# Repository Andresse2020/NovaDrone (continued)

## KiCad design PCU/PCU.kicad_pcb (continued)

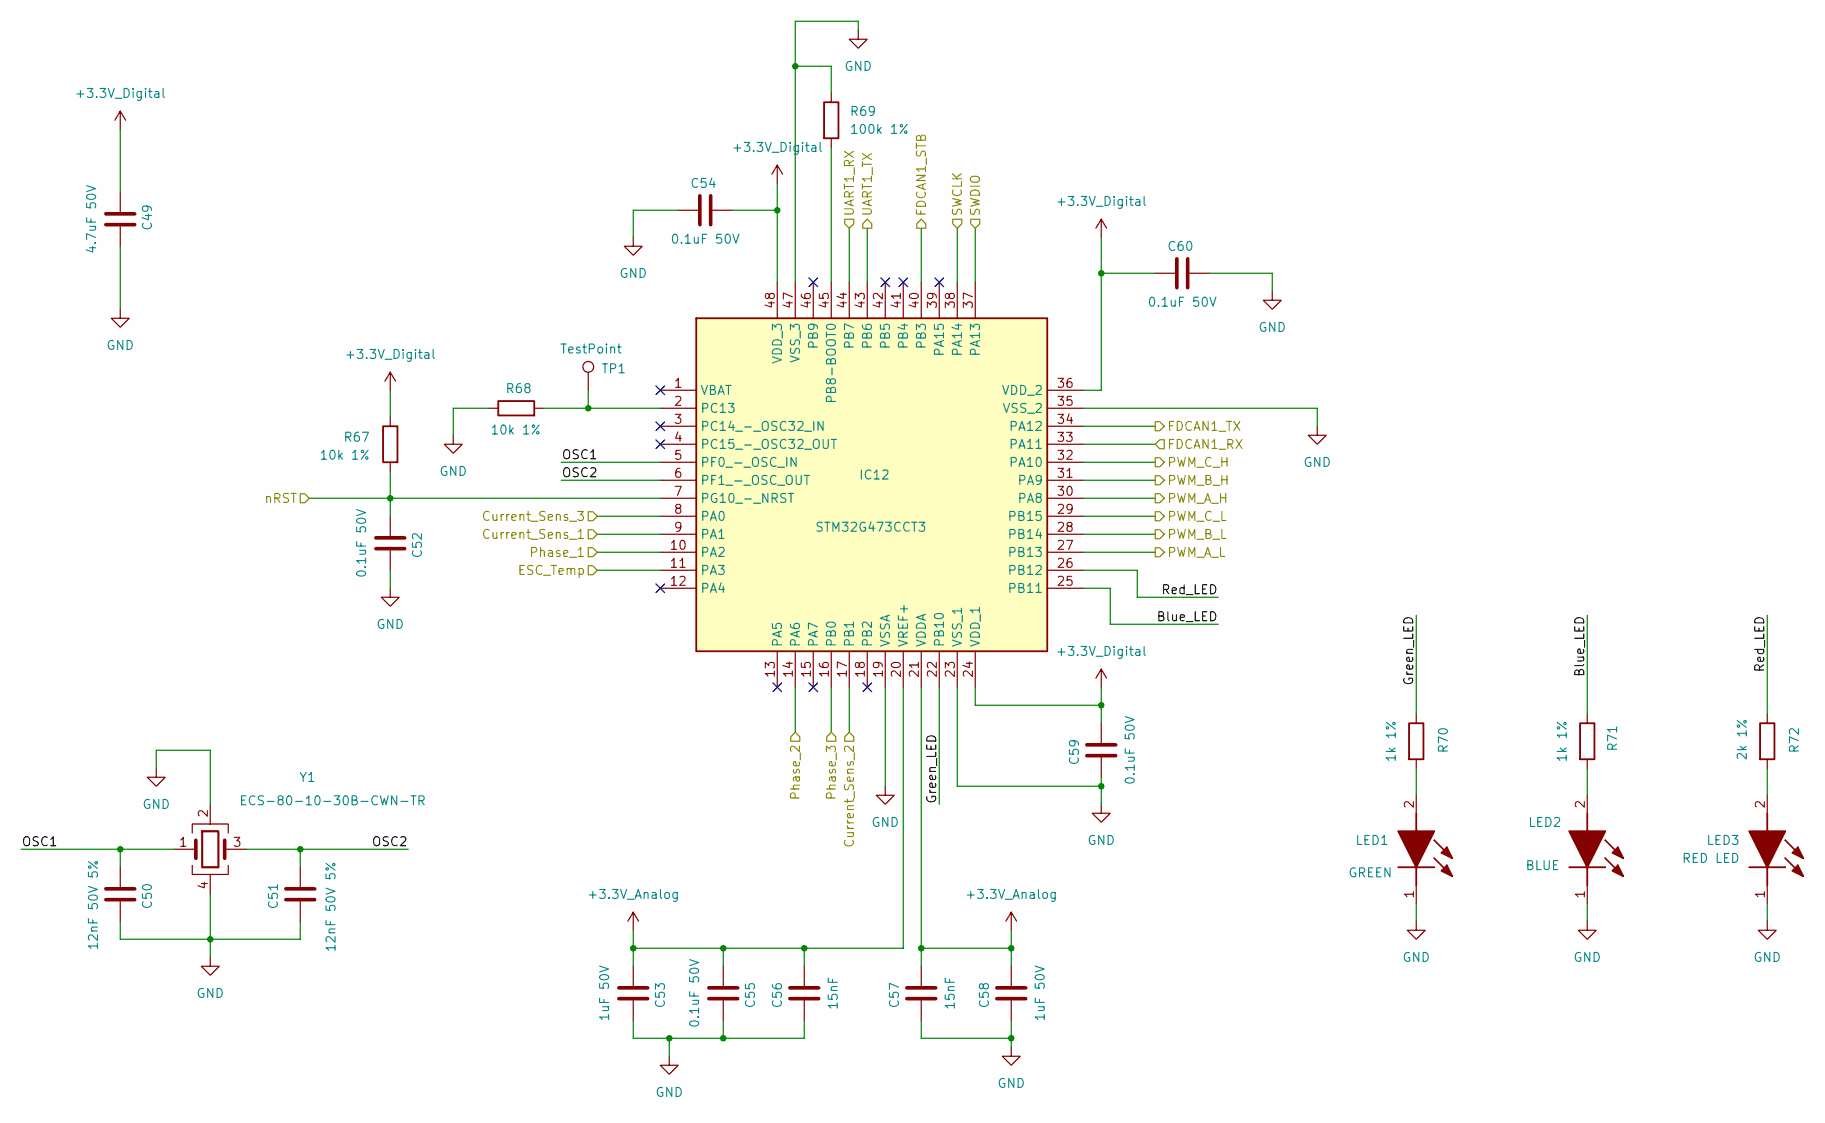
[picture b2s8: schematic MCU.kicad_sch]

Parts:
C49: 4.7uF 50V; C_1206_3216Metric; Manufacturer_Part_Number CL31B475KBHNFNE
C50, C51: 12nF 50V 5%; C_0603_1608Metric; Manufacturer_Part_Number 06035C120J4T2A
C52, C54, C55, C59, C60: 0.1uF 50V; C_0603_1608Metric; Manufacturer_Part_Number CL10B104KB85PNL
C53, C58: 1uF 50V; C_0805_2012Metric; Manufacturer_Part_Number CL21B105KBFNNNE
C56, C57: 15nF; C_0603_1608Metric; Manufacturer_Part_Number CL10B153KB8NNNC
IC12: STM32G473CCT3; QFP50P900X900X160-48N; Mouser Part Number 511-STM32G473CCT3
LED1: GREEN; LEDM168X80N; Mouser Part Number 604-APHD1608LZGCK
LED2: BLUE; LEDM168X80N; Mouser Part Number 604-APHD1608LQBCD
LED3: RED LED; LEDM168X80N; Manufacturer_Part_Number APHD1608LSURCK
R67, R68: 10k 1%; R_0603_1608Metric; Manufacturer_Part_Number AF0603FR-0710KL
R69: 100k 1%; R_0603_1608Metric; Manufacturer_Part_Number AT0603FRE07100KL
R70, R71: 1k 1%; R_0603_1608Metric; Manufacturer_Part_Number RT0603FRE071KL
R72: 2k 1%; R_0603_1608Metric; Manufacturer_Part_Number RE0603FRE072KL
TP1: TestPoint; TestPoint_Pad_D1.0mm
Y1: ECS-80-10-30B-CWN-TR; ECS801830BAGNTR; Mouser Part Number 520-80-10-30B-CWNT

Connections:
+3.3V_Analog: C53.2, C55.2, C56.2, C57.2, C58.2, IC12.20 (VREF+), IC12.21 (VDDA); also elsewhere on the board
+3.3V_Digital: C49.1, C54.2, C59.2, C60.1, IC12.24 (VDD_1), IC12.36 (VDD_2), IC12.48 (VDD_3), R67.1; also elsewhere on the board
/ESC_2/Current_Sens_1: IC12.9 (PA1); also elsewhere on the board
/ESC_2/Current_Sens_2: IC12.17 (PB1); also elsewhere on the board
/ESC_2/Current_Sens_3: IC12.8 (PA0); also elsewhere on the board
/ESC_2/ESC_Temp: IC12.11 (PA3); also elsewhere on the board
/ESC_2/MCU/Blue_LED: IC12.25 (PB11), R71.1
/ESC_2/MCU/FDCAN1_RX: IC12.33 (PA11); also elsewhere on the board
/ESC_2/MCU/FDCAN1_STB: IC12.40 (PB3); also elsewhere on the board
/ESC_2/MCU/FDCAN1_TX: IC12.34 (PA12); also elsewhere on the board
/ESC_2/MCU/Green_LED: IC12.22 (PB10), R70.1
/ESC_2/MCU/OSC1: C50.2, IC12.5 (PF0_-_OSC_IN), Y1.1
/ESC_2/MCU/OSC2: C51.2, IC12.6 (PF1_-_OSC_OUT), Y1.3
/ESC_2/MCU/PWM_A_H: IC12.30 (PA8); also elsewhere on the board
/ESC_2/MCU/PWM_A_L: IC12.27 (PB13); also elsewhere on the board
/ESC_2/MCU/PWM_B_H: IC12.31 (PA9); also elsewhere on the board
/ESC_2/MCU/PWM_B_L: IC12.28 (PB14); also elsewhere on the board
/ESC_2/MCU/PWM_C_H: IC12.32 (PA10); also elsewhere on the board
/ESC_2/MCU/PWM_C_L: IC12.29 (PB15); also elsewhere on the board
/ESC_2/MCU/Red_LED: IC12.26 (PB12), R72.1
/ESC_2/MCU/SWCLK: IC12.38 (PA14); also elsewhere on the board
/ESC_2/MCU/SWDIO: IC12.37 (PA13); also elsewhere on the board
/ESC_2/MCU/UART1_RX: IC12.44 (PB7); also elsewhere on the board
/ESC_2/MCU/UART1_TX: IC12.43 (PB6); also elsewhere on the board
/ESC_2/Phase_1: IC12.10 (PA2); also elsewhere on the board
/ESC_2/Phase_2: IC12.14 (PA6); also elsewhere on the board
/ESC_2/Phase_3: IC12.16 (PB0); also elsewhere on the board
/ESC_2_nRST: C52.2, IC12.7 (PG10_-_NRST), R67.2; also elsewhere on the board
GND: C49.2, C50.1, C51.1, C52.1, C53.1, C54.1, C55.1, C56.1, C57.1, C58.1, C59.1, C60.2, IC12.19 (VSSA), IC12.23 (VSS_1), IC12.35 (VSS_2), IC12.47 (VSS_3), LED1.1 (K), LED2.1 (K), LED3.1 (K), R68.1, R69.1, Y1.2, Y1.4; also elsewhere on the board
unnamed: IC12.45 (PB8-BOOT0), R69.2
unnamed: IC12.2 (PC13), R68.2, TP1.1
unnamed: LED1.2 (A), R70.2
unnamed: LED2.2 (A), R71.2
unnamed: LED3.2 (A), R72.2

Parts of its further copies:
C97, C145, C181: 4.7uF 50V; C_1206_3216Metric; Manufacturer_Part_Number CL31B475KBHNFNE
C98, C99, C146, C147, C182, C183: 12nF 50V 5%; C_0603_1608Metric; Manufacturer_Part_Number 06035C120J4T2A
C100, C102, C103, C107, C108, C148, C150, C151, C155, C156, C184, C186, C187, C191, C192: 0.1uF 50V; C_0603_1608Metric; Manufacturer_Part_Number CL10B104KB85PNL
C101, C106, C149, C154, C185, C190: 1uF 50V; C_0805_2012Metric; Manufacturer_Part_Number CL21B105KBFNNNE
C104, C105, C152, C153, C188, C189: 15nF; C_0603_1608Metric; Manufacturer_Part_Number CL10B153KB8NNNC
IC20, IC28, IC30: STM32G473CCT3; QFP50P900X900X160-48N; Mouser Part Number 511-STM32G473CCT3
LED4, LED7, LED13: GREEN; LEDM168X80N; Mouser Part Number 604-APHD1608LZGCK
LED5, LED8, LED14: BLUE; LEDM168X80N; Mouser Part Number 604-APHD1608LQBCD
LED6, LED9, LED15: RED LED; LEDM168X80N; Manufacturer_Part_Number APHD1608LSURCK
R125, R126, R183, R184, R201, R202: 10k 1%; R_0603_1608Metric; Manufacturer_Part_Number AF0603FR-0710KL
R127, R185, R203: 100k 1%; R_0603_1608Metric; Manufacturer_Part_Number AT0603FRE07100KL
R128, R129, R186, R187, R204, R205: 1k 1%; R_0603_1608Metric; Manufacturer_Part_Number RT0603FRE071KL
R130, R188, R206: 2k 1%; R_0603_1608Metric; Manufacturer_Part_Number RE0603FRE072KL
TP2, TP3, TP7: TestPoint; TestPoint_Pad_D1.0mm
Y2, Y3, Y4: ECS-80-10-30B-CWN-TR; ECS801830BAGNTR; Mouser Part Number 520-80-10-30B-CWNT

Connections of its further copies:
+3.3V_Analog: C101.2, C103.2, C104.2, C105.2, C106.2, C149.2, C151.2, C152.2, C153.2, C154.2, C185.2, C187.2, C188.2, C189.2, C190.2, IC20.20 (VREF+), IC20.21 (VDDA), IC28.20 (VREF+), IC28.21 (VDDA), IC30.20 (VREF+), IC30.21 (VDDA); also elsewhere on the board
+3.3V_Digital: C97.1, C102.2, C107.2, C108.1, C145.1, C150.2, C155.2, C156.1, C181.1, C186.2, C191.2, C192.1, IC20.24 (VDD_1), IC20.36 (VDD_2), IC20.48 (VDD_3), IC28.24 (VDD_1), IC28.36 (VDD_2), IC28.48 (VDD_3), IC30.24 (VDD_1), IC30.36 (VDD_2), IC30.48 (VDD_3), R125.1, R183.1, R201.1; also elsewhere on the board
/ESC_1/Current_Sens_1: IC30.9 (PA1); also elsewhere on the board
/ESC_1/Current_Sens_2: IC30.17 (PB1); also elsewhere on the board
/ESC_1/Current_Sens_3: IC30.8 (PA0); also elsewhere on the board
/ESC_1/ESC_Temp: IC30.11 (PA3); also elsewhere on the board
/ESC_1/MCU/Blue_LED: IC30.25 (PB11), R205.1
/ESC_1/MCU/FDCAN1_RX: IC30.33 (PA11); also elsewhere on the board
/ESC_1/MCU/FDCAN1_STB: IC30.40 (PB3); also elsewhere on the board
/ESC_1/MCU/FDCAN1_TX: IC30.34 (PA12); also elsewhere on the board
/ESC_1/MCU/Green_LED: IC30.22 (PB10), R204.1
/ESC_1/MCU/OSC1: C182.2, IC30.5 (PF0_-_OSC_IN), Y4.1
/ESC_1/MCU/OSC2: C183.2, IC30.6 (PF1_-_OSC_OUT), Y4.3
/ESC_1/MCU/PWM_A_H: IC30.30 (PA8); also elsewhere on the board
/ESC_1/MCU/PWM_A_L: IC30.27 (PB13); also elsewhere on the board
/ESC_1/MCU/PWM_B_H: IC30.31 (PA9); also elsewhere on the board
/ESC_1/MCU/PWM_B_L: IC30.28 (PB14); also elsewhere on the board
/ESC_1/MCU/PWM_C_H: IC30.32 (PA10); also elsewhere on the board
/ESC_1/MCU/PWM_C_L: IC30.29 (PB15); also elsewhere on the board
/ESC_1/MCU/Red_LED: IC30.26 (PB12), R206.1
/ESC_1/MCU/SWCLK: IC30.38 (PA14); also elsewhere on the board
/ESC_1/MCU/SWDIO: IC30.37 (PA13); also elsewhere on the board
/ESC_1/MCU/UART1_RX: IC30.44 (PB7); also elsewhere on the board
/ESC_1/MCU/UART1_TX: IC30.43 (PB6); also elsewhere on the board
/ESC_1/Phase_1: IC30.10 (PA2); also elsewhere on the board
/ESC_1/Phase_2: IC30.14 (PA6); also elsewhere on the board
/ESC_1/Phase_3: IC30.16 (PB0); also elsewhere on the board
/ESC_1_nRST: C184.2, IC30.7 (PG10_-_NRST), R201.2; also elsewhere on the board
/ESC_3/Current_Sens_1: IC20.9 (PA1); also elsewhere on the board
/ESC_3/Current_Sens_2: IC20.17 (PB1); also elsewhere on the board
/ESC_3/Current_Sens_3: IC20.8 (PA0); also elsewhere on the board
/ESC_3/ESC_Temp: IC20.11 (PA3); also elsewhere on the board
/ESC_3/MCU/Blue_LED: IC20.25 (PB11), R129.1
/ESC_3/MCU/FDCAN1_RX: IC20.33 (PA11); also elsewhere on the board
/ESC_3/MCU/FDCAN1_STB: IC20.40 (PB3); also elsewhere on the board
/ESC_3/MCU/FDCAN1_TX: IC20.34 (PA12); also elsewhere on the board
/ESC_3/MCU/Green_LED: IC20.22 (PB10), R128.1
/ESC_3/MCU/OSC1: C98.2, IC20.5 (PF0_-_OSC_IN), Y2.1
/ESC_3/MCU/OSC2: C99.2, IC20.6 (PF1_-_OSC_OUT), Y2.3
/ESC_3/MCU/PWM_A_H: IC20.30 (PA8); also elsewhere on the board
/ESC_3/MCU/PWM_A_L: IC20.27 (PB13); also elsewhere on the board
/ESC_3/MCU/PWM_B_H: IC20.31 (PA9); also elsewhere on the board
/ESC_3/MCU/PWM_B_L: IC20.28 (PB14); also elsewhere on the board
/ESC_3/MCU/PWM_C_H: IC20.32 (PA10); also elsewhere on the board
/ESC_3/MCU/PWM_C_L: IC20.29 (PB15); also elsewhere on the board
/ESC_3/MCU/Red_LED: IC20.26 (PB12), R130.1
/ESC_3/MCU/SWCLK: IC20.38 (PA14); also elsewhere on the board
/ESC_3/MCU/SWDIO: IC20.37 (PA13); also elsewhere on the board
/ESC_3/MCU/UART1_RX: IC20.44 (PB7); also elsewhere on the board
/ESC_3/MCU/UART1_TX: IC20.43 (PB6); also elsewhere on the board
/ESC_3/Phase_1: IC20.10 (PA2); also elsewhere on the board
/ESC_3/Phase_2: IC20.14 (PA6); also elsewhere on the board
/ESC_3/Phase_3: IC20.16 (PB0); also elsewhere on the board
/ESC_3_nRST: C100.2, IC20.7 (PG10_-_NRST), R125.2; also elsewhere on the board
/ESC_4/Current_Sens_1: IC28.9 (PA1); also elsewhere on the board
/ESC_4/Current_Sens_2: IC28.17 (PB1); also elsewhere on the board
/ESC_4/Current_Sens_3: IC28.8 (PA0); also elsewhere on the board
/ESC_4/ESC_Temp: IC28.11 (PA3); also elsewhere on the board
/ESC_4/MCU/Blue_LED: IC28.25 (PB11), R187.1
/ESC_4/MCU/FDCAN1_RX: IC28.33 (PA11); also elsewhere on the board
/ESC_4/MCU/FDCAN1_STB: IC28.40 (PB3); also elsewhere on the board
/ESC_4/MCU/FDCAN1_TX: IC28.34 (PA12); also elsewhere on the board
/ESC_4/MCU/Green_LED: IC28.22 (PB10), R186.1
/ESC_4/MCU/OSC1: C146.2, IC28.5 (PF0_-_OSC_IN), Y3.1
/ESC_4/MCU/OSC2: C147.2, IC28.6 (PF1_-_OSC_OUT), Y3.3
/ESC_4/MCU/PWM_A_H: IC28.30 (PA8); also elsewhere on the board
/ESC_4/MCU/PWM_A_L: IC28.27 (PB13); also elsewhere on the board
/ESC_4/MCU/PWM_B_H: IC28.31 (PA9); also elsewhere on the board
/ESC_4/MCU/PWM_B_L: IC28.28 (PB14); also elsewhere on the board
/ESC_4/MCU/PWM_C_H: IC28.32 (PA10); also elsewhere on the board
/ESC_4/MCU/PWM_C_L: IC28.29 (PB15); also elsewhere on the board
/ESC_4/MCU/Red_LED: IC28.26 (PB12), R188.1
/ESC_4/MCU/SWCLK: IC28.38 (PA14); also elsewhere on the board
/ESC_4/MCU/SWDIO: IC28.37 (PA13); also elsewhere on the board
/ESC_4/MCU/UART1_RX: IC28.44 (PB7); also elsewhere on the board
/ESC_4/MCU/UART1_TX: IC28.43 (PB6); also elsewhere on the board
/ESC_4/Phase_1: IC28.10 (PA2); also elsewhere on the board
/ESC_4/Phase_2: IC28.14 (PA6); also elsewhere on the board
/ESC_4/Phase_3: IC28.16 (PB0); also elsewhere on the board
/ESC_4_nRST: C148.2, IC28.7 (PG10_-_NRST), R183.2; also elsewhere on the board
GND: C97.2, C98.1, C99.1, C100.1, C101.1, C102.1, C103.1, C104.1, C105.1, C106.1, C107.1, C108.2, C145.2, C146.1, C147.1, C148.1, C149.1, C150.1, C151.1, C152.1, C153.1, C154.1, C155.1, C156.2, C181.2, C182.1, C183.1, C184.1, C185.1, C186.1, C187.1, C188.1, C189.1, C190.1, C191.1, C192.2, IC20.19 (VSSA), IC20.23 (VSS_1), IC20.35 (VSS_2), IC20.47 (VSS_3), IC28.19 (VSSA), IC28.23 (VSS_1), IC28.35 (VSS_2), IC28.47 (VSS_3), IC30.19 (VSSA), IC30.23 (VSS_1), IC30.35 (VSS_2), IC30.47 (VSS_3), LED4.1 (K), LED5.1 (K), LED6.1 (K), LED7.1 (K), LED8.1 (K), LED9.1 (K), LED13.1 (K), LED14.1 (K), LED15.1 (K), R126.1, R127.1, R184.1, R185.1, R202.1, R203.1, Y2.2, Y2.4, Y3.2, Y3.4, Y4.2, Y4.4; also elsewhere on the board
unnamed: IC20.45 (PB8-BOOT0), R127.2
unnamed: IC20.2 (PC13), R126.2, TP2.1
unnamed: IC28.45 (PB8-BOOT0), R185.2
unnamed: IC28.2 (PC13), R184.2, TP3.1
unnamed: IC30.45 (PB8-BOOT0), R203.2
unnamed: IC30.2 (PC13), R202.2, TP7.1
unnamed: LED4.2 (A), R128.2
unnamed: LED5.2 (A), R129.2
unnamed: LED6.2 (A), R130.2
unnamed: LED7.2 (A), R186.2
unnamed: LED8.2 (A), R187.2
unnamed: LED9.2 (A), R188.2
unnamed: LED13.2 (A), R204.2
unnamed: LED14.2 (A), R205.2
unnamed: LED15.2 (A), R206.2

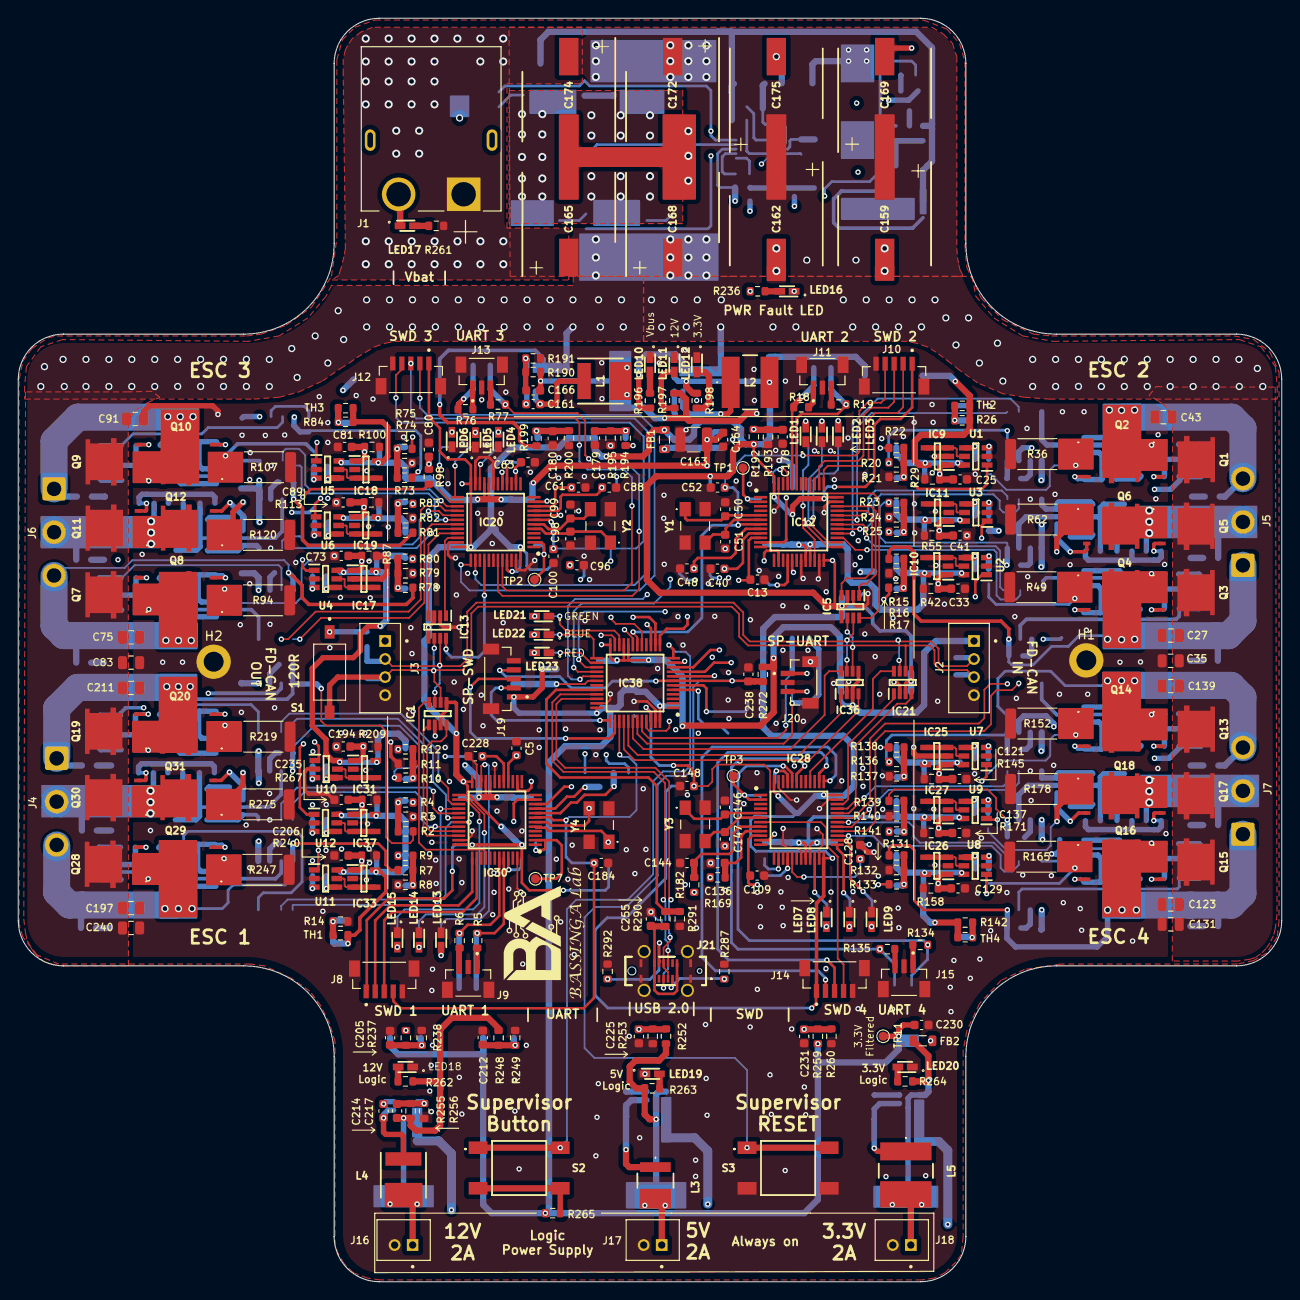
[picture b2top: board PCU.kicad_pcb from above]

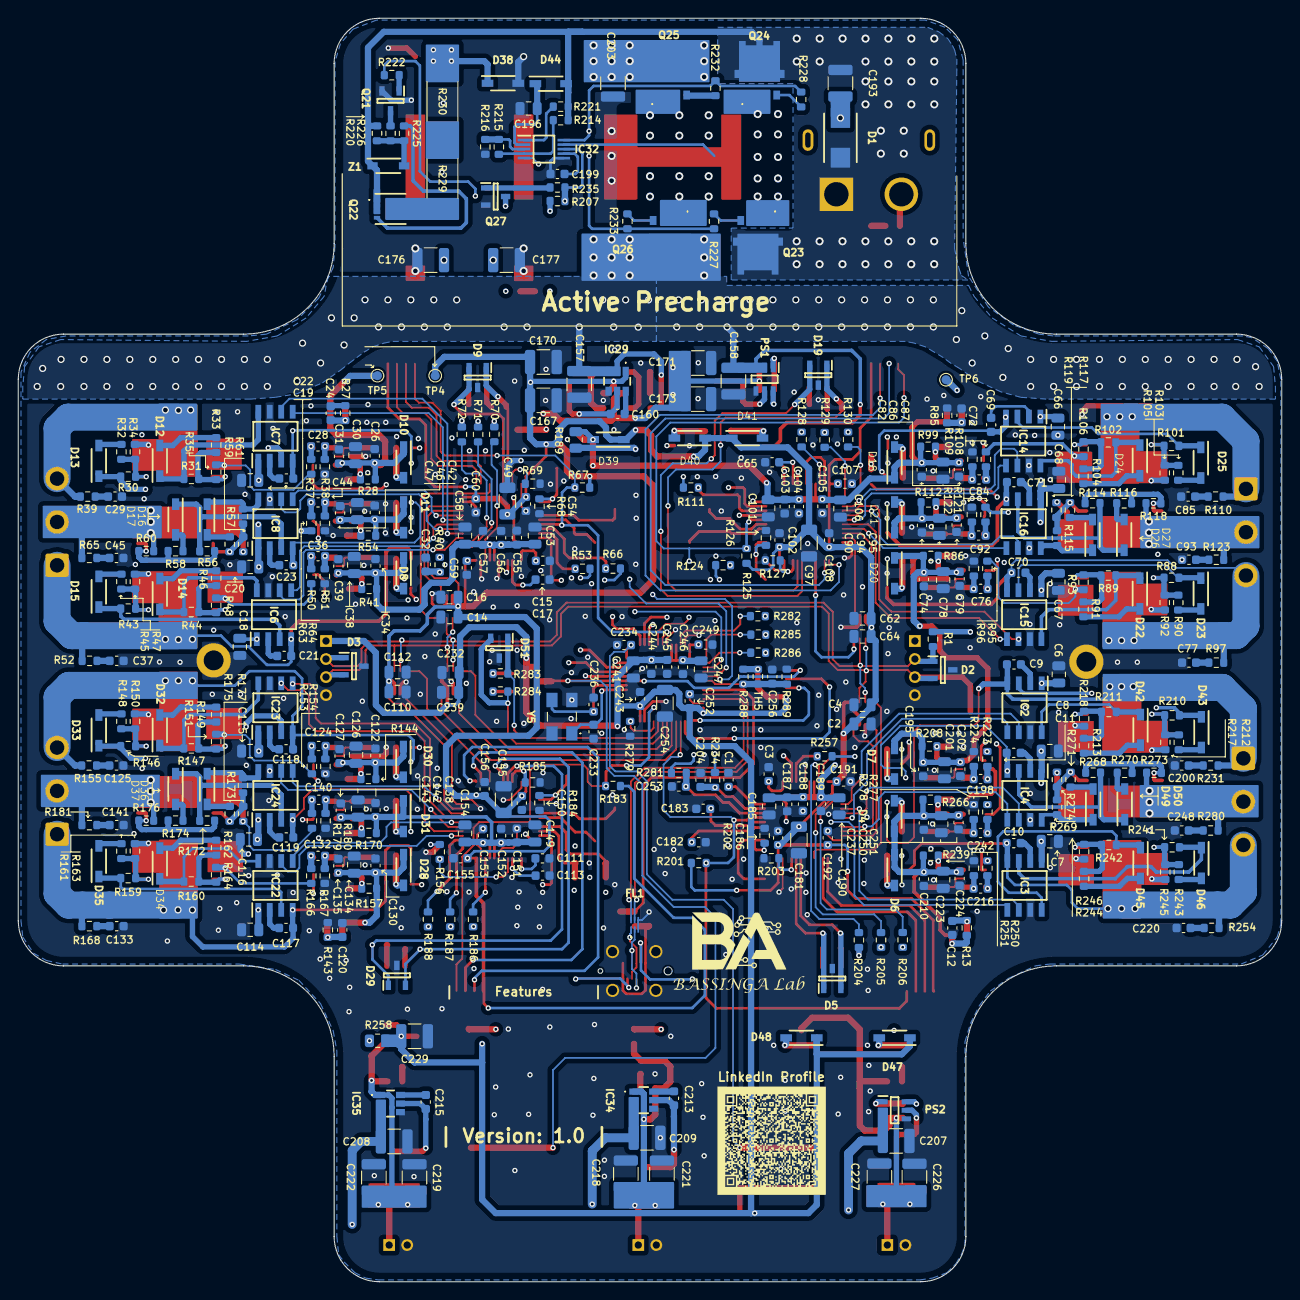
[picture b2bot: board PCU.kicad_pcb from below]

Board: 4 copper layers, 140.0 x 140.0 mm, 757 parts (451 on the bottom side), 418 nets.

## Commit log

2025-07-06 End of Inverter design
2025-07-07 PCB temperature measurement
2025-07-14 Interfaces Update
2025-07-18 Power Supply
2025-07-18 Rename project
2025-07-19 Power Supply Update
2025-07-21 End of Schematic
2025-07-21 Start of PCB Layout
2025-07-22 PCB Layout Update
2025-08-04 PCB nearly completed
2025-08-05 End of Placement
2025-08-06 PCB End of Routing
2025-08-07 End of PCB Routing
2025-08-17 BOM Update
2025-10-18 Docs folder Added
2025-11-09 Propulsion Control Unit - Started
2025-11-10 ESC Block Updated
2025-11-11 high power supply block
2025-11-14 Active precharge Block
2025-11-15 Logic PSU Completed
2025-11-16 Supervisor Block
2025-11-17 Start of PCB Design
2025-11-18 Readme update
2025-11-21 PCB Design started
2025-11-24 Component Placement
2025-11-25 Precharge Block Routed
2025-11-26 PSU Blocks Routed
2025-12-01 Power stage routed
2025-12-01 Drivers routed
2025-12-03 All components placed
2025-12-05 Analog Signal Routing started
2025-12-06 ESCs Analog signals routed
2025-12-06 All analog signals routed
2025-12-07 Analog trace optimization
2025-12-08 Digital high speed routing started
2025-12-09 Gigital high speed signal routed
2025-12-10 PWM Signals routed
2025-12-11 Digital signal routed
2025-12-12 Digital signals routed
2025-12-15 Logic power supply routed
2025-12-17 All track routed
2025-12-19 Silkscreen add
2025-12-20 End of Design
2025-12-22 Update firmware with license
2025-12-22 Add Creative Commons license
    Added the Creative Commons Attribution-NonCommercial-ShareAlike 4.0 International Public License to the project.
2025-12-23 Update license from Creative Commons to CERN OHL v2
    Replaced Creative Commons license with CERN Open Hardware Licence Version 2 - Weakly Reciprocal.
2025-12-23 Revise licensing section in README.md
    Updated licensing information for hardware and firmware.
2025-12-23 Remove firmware architecture section from README
2025-12-23 Update LICENSE with copyright and licensing information
2025-12-23 Update README with copyright and license details
    Added copyright and licensing information to README.
2026-01-03 Update connector type from XT90 to XT60
2026-01-03 Components library added
2026-01-03 Fly controller design started
2026-01-03 Remove modular firmware details from README
    Removed mention of modular firmware structure.
2026-01-03 Add CODEOWNERS file for project ownership
2026-02-17 FC requirements added
2026-02-19 RC Module Added
2026-02-19 GNSS & Compass Module Added
2026-02-19 Project Lib Added
